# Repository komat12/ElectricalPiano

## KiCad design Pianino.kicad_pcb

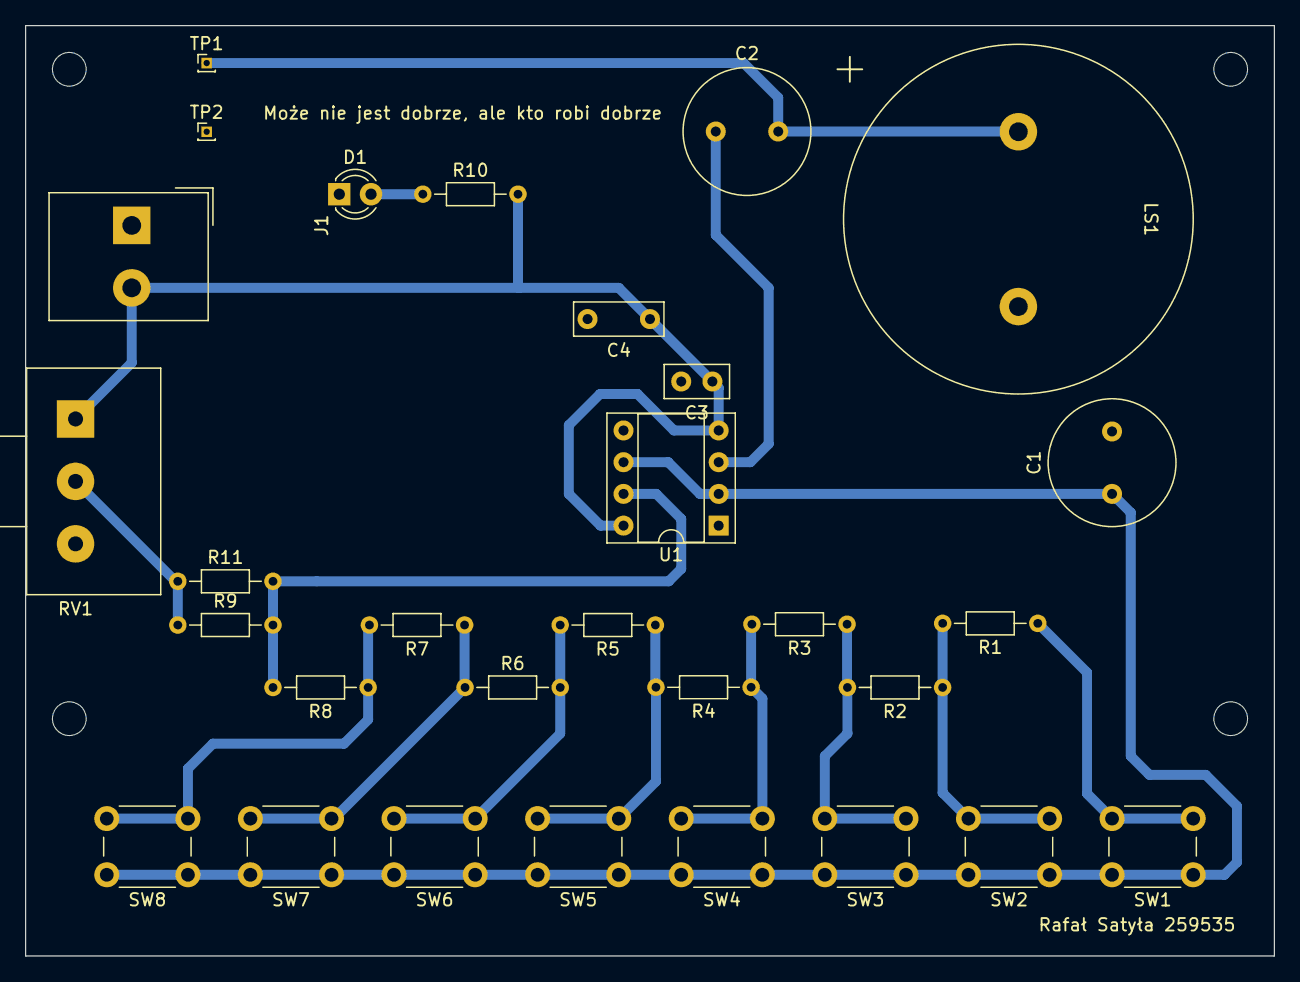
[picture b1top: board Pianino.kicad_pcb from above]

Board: 2 copper layers, 100.0 x 74.5 mm, 34 parts (0 on the bottom side), 16 nets.

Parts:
C1: C_Trim; C_Radial_D10.0mm_H12.5mm_P5.00mm
C2: C_Polarized; C_Radial_D10.0mm_H12.5mm_P5.00mm
C3: C_Small; C_Disc_D5.0mm_W2.5mm_P2.50mm
C4: C_Small; C_Disc_D7.0mm_W2.5mm_P5.00mm
D1: LED; LED_D3.0mm
H1, H2, H3, H4: MountingHole; MountingHole_2.7mm
J1: Screw_Terminal_01x02; Altech_AK300_1x02_P5.00mm_45-Degree
LS1: Speaker; Speaker_botland
R1, R2, R3, R4, R5, R6, R7, R8, R9, R10, R11: R; R_Axial_DIN0204_L3.6mm_D1.6mm_P7.62mm_Horizontal
RV1: R_Potentiometer; Potentiometer_Alps_RK163_Single_Horizontal
SW1, SW2, SW3, SW4, SW5, SW6, SW7, SW8: SW_MEC_5E; SW_PUSH_6mm_H8mm
TP1, TP2: TestPoint; PinHeader_1x01_P1.00mm_Vertical
U1: NE555P; DIP-8_W7.62mm_Socket

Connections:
+9V: C3.1, C4.1, J1.2, R10.2, RV1.1, U1.4 (R), U1.8 (VCC)
GND: C1.2, C3.2, C4.2, D1.1 (K), J1.1, LS1.2, TP2.1, U1.1 (GND)
unnamed: C1.1, SW1.1, SW2.1, SW3.1, SW4.1, SW5.1, SW6.1, SW7.1, SW8.1, U1.2 (TR), U1.6 (THR)
unnamed: C2.1, U1.3 (Q)
unnamed: C2.2, LS1.1, TP1.1
unnamed: D1.2 (A), R10.1
unnamed: R1.1, SW1.2
unnamed: R1.2, R2.1, SW2.2
unnamed: R2.2, R3.1, SW3.2
unnamed: R3.2, R4.1, SW4.2
unnamed: R4.2, R5.1, SW5.2
unnamed: R5.2, R6.2, SW6.2
unnamed: R6.1, R7.1, SW7.2
unnamed: R7.2, R8.1, SW8.2
unnamed: R8.2, R9.2, R11.2, U1.7 (DIS)
unnamed: R9.1, R11.1, RV1.2
